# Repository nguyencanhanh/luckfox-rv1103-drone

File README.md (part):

# Drone AI trên RV1103 (Luckfox Pico Mini B)

Nguyên mẫu quadcopter dùng **một chip Rockchip RV1103**:
- **Cortex-A7 chạy Linux:** camera, NPU nhận dạng, Wi-Fi, GPS, bộ thu RC.
- **Lõi MCU RISC-V (HPMCU) chạy RT-Thread:** vòng điều khiển bay 1 kHz.

Mục tiêu dự án là trả lời bằng số liệu đo được: **kiến trúc một chip có bay được không**. Nếu không, phương án B là thêm một MCU điều khiển bay rời.

> **Trạng thái (2026-09-27):** chưa bay thật.
> - Linux và MCU đã chạy song song trên board, vòng 1 kHz đã đo.
> - Phần mềm bay chạy đầy đủ trong mô phỏng và lái được trong 3D.
> - Mạch bay LFX_FC_R1 đã thiết kế xong, chưa sản xuất.
> - Chưa có driver cảm biến thật, chưa xuất PWM ra ESC. Motor chưa bao giờ được cấp lệnh.

## Mục lục

- [Trạng thái theo mốc](#trạng-thái-theo-mốc)
- [Kiến trúc](#kiến-trúc)
- [Phần cứng: mạch bay LFX_FC_R2](#phần-cứng-mạch-bay-lfx_fc_r2)
- [Mô phỏng](#mô-phỏng)
- [Bắt đầu nhanh](#bắt-đầu-nhanh)
- [Cấu trúc repo](#cấu-trúc-repo)
- [An toàn](#an-toàn)
- [Tài liệu](#tài-liệu)
- [Nguồn tham khảo](#nguồn-tham-khảo)
- [License](#license)

## Trạng thái theo mốc

| Mốc | Nội dung | Kết quả | Bằng chứng |
|---|---|---|---|
| 01 | Điều tra phần cứng RV1103, HPMCU trong SDK | xong | [RV1103_MCU.md](docs/RV1103_MCU.md), [PERIPHERALS.md](docs/PERIPHERALS.md) |
| 02 | Build firmware Luckfox stock trên macOS | **PASS** | `logs/sdk_build.log`, [MILESTONE1.md](docs/MILESTONE1.md) |
| 03 | Build RT-Thread cho HPMCU | **PASS** | [MCU_BUILD.md](docs/MCU_BUILD.md) |
| 04 | MCU chạy song song Linux, vòng 1 kHz | **PASS trên board**: 2 × 1 000 000 vòng, 0 lỡ chu kỳ; jitter 18,2 µs lúc idle, 116,7 µs khi camera chạy | [REALTIME.md](docs/REALTIME.md) |
| — | Mạch bay LFX_FC_R1 (46 × 46 mm, 4 lớp) | thiết kế xong: ERC 0, DRC 0, 0 nối hở, khớp sơ đồ | [phần cứng](#phần-cứng-mạch-bay-lfx_fc_r1) |
| 05 | Phần mềm bay + mô phỏng SITL + 3D | **77/77 unit test, 10/10 kịch bản bay** (×2 profile cảm biến), kiểm thử bàn phím end-to-end 6/6 | [simulator/README.md](simulator/README.md) |
| 05b | Phần mềm bay chạy trên HPMCU với cảm biến giả (đo thời gian) | build xong (53 KB), **chưa chạy**: board chưa cắm | `tools/run_fc_mcu.sh` |
| 06–07 | Driver SPI + ICM-42688-P trên MCU | chưa làm: cần module IMU để kiểm | |
| 11 | Xuất PWM / DShot, đo bằng logic analyzer | chưa làm, **không gắn cánh** | |
| 12–13 | Điều khiển từ xa: IPC Linux ↔ MCU, `rc-bridge` (ELRS + mạng), trạm mặt đất có camera | **code xong, chuỗi đầy đủ chạy trên Mac 7/7**; build cho board xong, **chưa chạy trên board**; bộ thu ELRS cần chuyển console khỏi UART2 | [ground/README.md](ground/README.md) |
| M3 | Camera → NPU → nhận dạng, Wi-Fi, telemetry | chưa làm | |

Kế hoạch đầy đủ theo thứ tự an toàn ở mục [An toàn](#an-toàn).

## Kiến trúc

| Miền | Chạy gì | Sở hữu phần cứng |
|---|---|---|
| **HPMCU** RISC-V SCR1 297 MHz, `rv32imc` (không FPU), RT-Thread | vòng tốc độ quay 1 kHz, vòng góc 250 Hz, vòng độ cao 100 Hz, trộn motor, ARM / failsafe | SPI0 (IMU, barometer), PWM2 kênh 8–11 (4 ESC) |
| **Cortex-A7** 1,1 GHz, Linux (Buildroot của SDK) | đọc bộ thu RC (CRSF), camera + NPU, điều hướng, LTE + GPS (module Lierda), telemetry Wi-Fi, nạp firmware MCU và Lierda | UART2 (bộ thu RC), UART3 (Lierda: AT, GNSS, nạp firmware), chân 18/20 (RESET/BOOT Lierda), MIPI CSI, USB, SARADC, CRU |
| **DDR chung** 64 MB | MCU chạy ở `0x01800000` (256 KB, đã kiểm chứng); IPC đề xuất ở `0x01840000` | [MEMORY_MAP.md](docs/MEMORY_MAP.md) |

Luồng điều khiển:

```
IMU 1 kHz ─► hiệu chuẩn ─► lọc ─► Mahony (góc) + baro/accel (độ cao)
          ─► PID góc / độ cao ─► PID tốc độ quay ─► trộn quad-X ─► 4 motor (0..1)
tay điều khiển ELRS ─► bộ thu (CRSF 420 kbaud) ─► Linux ─► IPC ─► MCU (lệnh lái, ARM, chế độ)
```

Code bay (`mcu/`) là C99 thuần, chỉ dùng float, không cấp phát động. Cùng một mã nguồn build cho:
- máy Mac (mô phỏng);
- MCU (RT-Thread).

Chỗ đổi duy nhất là nguồn dữ liệu cảm biến:
- `SIM_SENSOR`: cảm biến giả trong mô phỏng;
- `REAL_SENSOR`: driver thật (bước 06–07).

Chi tiết và rủi ro: [ARCHITECTURE.md](docs/ARCHITECTURE.md), [architecture.html](docs/architecture.html).

**Rủi ro lớn nhất của kiến trúc một chip:**

| Rủi ro | Hệ quả |
|---|---|
| HPMCU không có FPU | code bay chạy bằng soft-float; phải đo thời gian thật |
| HAL MCU của RV1106 không có SPI và UART | phải tự viết driver |
| Tải camera làm jitter MCU tăng 6,4 lần | ảnh hưởng độ ổn định vòng điều khiển |
| Tín hiệu RC đi qua Linux | Linux treo là mất RC; MCU phải tự vào failsafe |

## Phần cứng: mạch bay LFX_FC_R2

**Một board 50 × 50 mm** gồm mạch bay cho Luckfox Pico Mini B và module **LTE Cat.1 bis + GNSS** (Lierda NT26-KCN E, khay nano-SIM, 2 cổng U.FL). Thiết kế bằng pipeline KiCad 10 viết bằng script, trong [`hardware/LFX_FC_R2/`](hardware/LFX_FC_R2): `design.py` → sơ đồ → PCB → file sản xuất.

| Mặt trên | Mặt dưới | 3D |
|---|---|---|
|  |  |  |

Module Lierda và đế cắm Luckfox chưa có mô hình 3D trong KiCad nên trên ảnh render chỉ thấy pad của chúng.

**Thông số:**
- **Kích thước:** 50 × 50 mm, 4 lớp: F.Cu tín hiệu / GND / VSYS (+ đảo 3,3 V cảm biến, đảo 3,8 V dưới module LTE, đảo GND dưới đường anten) / B.Cu.
- **Lỗ bắt vít:** 4 lỗ M3, khoảng cách lỗ **39 × 39 mm**, cách mép 5,5 mm.
- **Nguồn vào:** pin 2S–6S, hàn vào pad BAT+ / BAT− (mặt trên, phía trước bên phải).
- **Mạch nguồn:**
  - TVS SMAJ33A và ferrite chặn xung, lọc nhiễu.
  - Buck TPS54360 ra 5 V (theo thiết kế mẫu TI SLVSBB4G), ngưỡng UVLO 6,44 V. Đặt ở mặt dưới dải phải, cách IMU khoảng 15 mm, có lớp GND In1 ở giữa.
  - Diode lý tưởng LM66100 cấp VSYS cho Luckfox; LDO TLV75533 cấp 3,3 V riêng cho cảm biến.
  - Buck TLV62569 hạ +5 V xuống **3,8 V** cho module LTE. VBAT của module chỉ chịu 3,3–4,5 V, nên không lấy thẳng từ pin.
- **Cảm biến trên SPI0:** IMU ICM-42688-P và barometer BMP390, đặt dưới Luckfox; 4 đường SPI của IMU vẽ tay, không dùng via.
- **GPS ngoài (thêm 2026-10-04):** chân 14 (GPIO1_D2) thành **UART5_RX** cho cổng J18; chân chọn chip của barometer chuyển sang chân 15 (GPIO1_D3, MCU điều khiển như GPIO), bỏ chân ngắt dự phòng của IMU (IMU đọc kiểu polling). GNSS trong module Lierda vẫn giữ nguyên.
- **Motor:** 4 cặp pad S/G ở 4 góc cho **4 ESC rời** (PWM8–11, điện trở 47 Ω). Không còn cổng ESC 4-in-1.
- **LTE + GNSS: Lierda NT26-KCN E** ở mặt dưới, nửa trước. Khi đặt mua chọn bản **GPS + BDS**: bản NT26KCNE20GNB trong sổ tay phần cứng chỉ có BeiDou, chân ra giống hệt.
  - UART3 của Luckfox (chân 12/13) đi qua 2 con SN74LVC1T45 để chuyển 3,3 V ↔ 1,8 V. Chip này tự cách ly khi module tắt, vì UART của module không chịu điện áp ngược. Cùng một UART dùng cho lệnh AT, đọc GNSS và nạp firmware (921600 bd).
  - **Luckfox nạp firmware cho Lierda:** chân 18 kéo RESET_N qua MOSFET; chân 20 (GPIO4_C1, bank 1,8 V, cùng mức với module) nối USB_BOOT qua 1 kΩ. Giữ BOOT mức cao rồi reset ≥ 300 ms là module vào chế độ nạp. Có test pad USB (D+/D−/VBUS) để nạp cứu bằng máy tính.
  - Khay **nano-SIM** có nắp bản lề ở mặt trên, giữa phía trước; điện trở 22 Ω, tụ 33 pF, chống ESD TPD4E05U06.
  - 2 cổng U.FL ở 2 góc trước mặt dưới: GNSS bên trái, LTE bên phải. Đường 50 Ω rộng 0,35 mm trên B.Cu, có mạch π để chỉnh phối hợp trở kháng. GNSS cấp nguồn 3,3 V cho anten active; dùng anten thụ động thì bỏ R43.
  - Còi được điều khiển từ chân AGPIO5 (pad 97, ở mép module) của Lierda, vì Luckfox đã hết chân.
  - **Không bật chế độ ngủ của module** (`AT+QSCLK=1`): khi ngủ, VDD_EXT tắt nên bộ chuyển mức cách ly, Luckfox không đánh thức được qua UART.

**Đầu cắm và pad:**

| Cổng | Chân | Ghi chú |
|---|---|---|
| J2 / J3 · pad pin | BAT+ / BAT− | dây XT30 từ pin, cùng dây cấp cho 4 ESC |
| J4 · bộ thu RC ELRS | 1 5 V, 2 GND, 3 TX board → RX bộ thu, 4 RX board ← TX bộ thu | UART2, CRSF; R24 1 kΩ kéo lên để bộ thu không kẹt bootloader |
| J6 · còi | 1 +5 V, 2 còi − (MOSFET đóng ngắt) | gate do AGPIO5 của Lierda điều khiển |
| **J18 · module GPS ATGM336H** | 1 VCC +5 V, 2 GND, 3 TXD module → RX board, 4 RXD (không nối), 5 PPS (không nối) | header 2,54 mm 5 chân nằm ngang ở mép trái, **cùng thứ tự chân với module ATGM336H 5 chân**: thân nhựa trên board, chân cong chìa ra ngoài mép để cắm dây Dupont 5 sợi thẳng sang module (lọt dưới vỏ canopy). UART5 chỉ nhận (chân 14), NMEA 9600 mặc định; RXD và PPS bỏ trống vì Luckfox hết chân. Chống ESD TPD1E05U06 + 33 Ω. +5 V lấy từ buck TPS54360 (cùng nguồn với bộ thu RC J4, đường mặt dưới sát mép trái), nên GPS chỉ có điện khi cắm pin, không chạy khi chỉ cắm USB |
| J7–J14 · pad ESC | S / G ở 4 góc | M1 sau-phải, M2 trước-phải, M3 sau-trái, M4 trước-trái (Betaflight) |
| J15 · nano-SIM | | GCT SIM8060, nắp bản lề |
| J16 · U.FL LTE / J17 · U.FL GNSS | | mặt dưới, 2 góc trước |
| TP1–TP3, TP5, TP6 | +5 V, VSYS, +3V3S, RC_TX, RC_RX | TP5/TP6: xem console khi rút bộ thu |
| TP7–TP13 | +3V8, VDD_EXT 1,8 V, USB D+, USB D−, USB VBUS, DBG TX, DBG RX của Lierda | nạp cứu / xem log module |

**Kiểm tra:** ERC 0, DRC 0 vi phạm / 0 cảnh báo, 0 nối hở, 0 lỗi khớp sơ đồ (`--schematic-parity`).

**Bộ file sản xuất** (Gerber, khoan, BOM, vị trí linh kiện, STEP) do `make_fab.py` tạo ra `fab/`. Thư mục này không lưu trong git.

**Cần làm trước khi đặt hàng:**
- BOM chưa có mã linh kiện cụ thể (MPN).
- Nên chọn xi **ENIG**: IMU, barometer là chip chân LGA và module Lierda là LCC + LGA 109 chân, cần pad phẳng.

### Lắp drone: khung LFX_FRAME_R1, động cơ không chổi than, 4 ESC rời

| Khung (in 3D) | Lắp đủ: khung + board + vỏ + motor + ESC + pin | Nhìn từ trên |
|---|---|---|
|  |  |  |

**Khung [`hardware/LFX_FRAME_R1`](hardware/LFX_FRAME_R1)** dựng bằng FreeCAD (script tham số `frame_freecad.py`), in 3D, cho **motor 1503 + cánh 3,5"**:
- Tấm giữa dày 3 mm: board bắt thẳng bằng **4 cột M3 dài 8 mm** vào lỗ 39 × 39, không cần tấm chuyển. Có 2 khe dây buộc pin 15 mm, lỗ khoét giảm nhẹ, 2 lỗ phía sau để buộc ống anten. Mặt dưới tấm giữa phẳng để kê pin.
- 4 tay đòn kiểu X, dày 5 mm, rộng 13 mm. Đế motor Ø22 mm có **rãnh M2 hướng tâm** (bán kính 4,3–6,6 mm): lắp được motor 1503 (4 × M2 theo hình vuông 9 × 9 mm) và các motor có lỗ trên vòng Ø9 mm. Lỗ giữa Ø7 mm cho trục và phe gài.
- **Khoảng cách motor do script tự tìm:** đẩy dần motor ra xa cho tới khi cánh 3,5" (thêm 2 mm dự phòng) không chạm vỏ canopy. Kết quả: motor cách tâm 63 mm theo mỗi trục (đường chéo trục 178 mm), khung 148 × 148 mm.
- 4 ESC buộc dây rút lên tay đòn, nằm ngoài vỏ; pin buộc dưới tấm giữa.
- In: PETG (hoặc PLA-CF), 5 lớp viền, infill 40 %. Khối lượng đặc khoảng 34 g.
- Đổi motor hoặc cánh: sửa `PROP_D`, `MOTOR_D`, `MOTOR_SLOT` ở đầu `frame_freecad.py` rồi chạy lại trong FreeCAD; khoảng cách motor tự tính lại.

**Linh kiện mua thêm:**

| Linh kiện | Gợi ý | Ghi chú |
|---|---|---|
| Motor ×4 | 1503, bản KV dành cho cánh 3,5" và đúng số cell pin (người bán thường ghi "3.5 inch 3S" hoặc "4S") | khoảng 8–9 g/con; 4 × M2 lỗ 9 × 9 mm |
| ESC ×4 | ESC rời 20–30 A, BLHeli_S / BLHeli_32 / AM32, chịu 2–4S | 1503 + cánh 3,5" kéo dòng cao hơn hẳn 1103, ESC 12 A không đủ |
| Cánh | 3,5" (3520 / 3525, 2–3 lá), lỗ trục hợp motor | |
| Pin | LiPo 3S hoặc 4S 450–650 mAh, đầu XT30 | |
| Cột M3 | 4 × 8 mm (khung → board) | |
| Anten | LTE dạng dán (FPC) + GNSS 25 × 25 mm (active 3,3 V hoặc thụ động), đầu U.FL | anten GNSS đặt trong hốc trên nóc vỏ |

**Đấu nối:**
```
Pin 3S/4S ─ XT30 ─┬─ nguồn 4 ESC (đỏ / đen)
                  └─ BAT+ / BAT− (J2 / J3) trên board
ESC n: tín hiệu → pad S, mass tín hiệu → pad G ở góc của motor n
   M1 sau-phải J7/J11 · M2 trước-phải J8/J12 · M3 sau-trái J9/J13 · M4 trước-trái J10/J14
Motor: 3 dây vào ESC; quay ngược chiều thì đổi 2 dây bất kỳ
```
- Board chạy 2S–6S (buck 5 V khởi động từ 6,44 V), nên 3S và 4S đều dư.
- ESC rời không có chân báo dòng, nên chỉ đo được áp pin (ADC_VBAT), không đo được dòng.

**Trọng lượng ước tính** (chưa cân thực tế):
- Board R2 khoảng 16 g, Luckfox + camera khoảng 8 g, 4 ESC khoảng 24 g, 4 motor 1503 khoảng 36 g, khung khoảng 34 g, vỏ khoảng 13 g, cánh khoảng 6 g, anten + ốc + dây khoảng 8 g, pin 4S 450 mAh khoảng 55 g (3S khoảng 40 g).
- Tổng **khoảng 200 g với 4S** (khoảng 185 g với 3S).
- Theo [bảng tra của Oscar Liang](https://oscarliang.com/table-prop-motor-lipo-weight/), cánh 3–3,5" với motor cỡ 1404–1505 trên 3S–4S hợp drone nặng khoảng 150–300 g, nên cấu hình này nằm giữa dải, dư lực. Mình chưa có số đo lực đẩy cụ thể của 1503; hãy xem bảng lực đẩy của đúng mẫu motor khi mua.

### Vỏ in 3D: LFX_CANOPY_R1

| Vỏ | Nhìn xuyên (kiểm tra lắp) | Phía sau |
|---|---|---|
|  |  |  |

Vỏ che board, dựng bằng **FreeCAD 1.1** (script tham số [`canopy_freecad.py`](hardware/LFX_CANOPY_R1/canopy_freecad.py), chạy trong FreeCAD hoặc qua addon [freecad-mcp](https://github.com/neka-nat/freecad-mcp)). Script dựng cả cụm lắp ráp từ file STEP của board (KiCad) cộng khối đại diện cho Luckfox, camera, Lierda, cột đỡ, rồi **kiểm tra va chạm**: không chạm.

- File in: [`canopy.stl`](hardware/LFX_CANOPY_R1/canopy.stl) (và `canopy.step`), 58 × 60 × 29 mm, khoảng 13 g PETG.
- Thành 1,2 mm (3 lớp viền với đầu phun 0,4 mm), bo tròn mọi cạnh, lỗ ống kính vát mép.
- Camera SC3336 áp vào mặt trong thành trước, có gờ định vị 4 phía; cố định bằng băng dính 2 mặt hoặc keo nến.
- Lỗ USB-C phía sau, nên **vẫn cắm cáp nạp code cho Luckfox khi đã đậy vỏ**.
- Hai bên hông để trống phía dưới cho dây RC, còi, ESC, dây pin và cáp U.FL; khe thông gió ngay trên Luckfox.
- Trên nóc có hốc lõm 0,8 mm đặt anten GNSS loại 25 × 25 mm (nằm trên cùng, nhìn thẳng lên trời) và lỗ luồn cáp; mặt nóc vẫn phẳng để in úp.
- 4 trụ rỗng tì xuống board tại 4 lỗ 39 × 39; vít **M3 × 25** xuyên trụ, qua board, vào cột đỡ.
- In: úp nóc xuống bàn in, PETG, không cần support.
- Sửa kích thước: đổi tham số đầu file `canopy_freecad.py` rồi chạy lại trong FreeCAD. File STEP của board xuất bằng `kicad-cli pcb export step` vào `hardware/LFX_CANOPY_R1/step/`.

### Phiên bản cũ

Vẫn giữ trong repo, DRC sạch, nhưng không còn là thiết kế chính:
- [`LFX_FC_R1`](hardware/LFX_FC_R1): mạch bay 46 × 46 mm, cổng ESC 4-in-1 (J1), cổng J5 nối sang board LTE ([ảnh](docs/img/pcb/3d_iso.jpg)).
- [`LFX_LTE_R1`](hardware/LFX_LTE_R1): board LTE 46 × 46 mm xếp tầng trên R1 ([ảnh](docs/img/pcb/lte_3d_iso.jpg)).
- [`LFX_MOUNT_R1`](hardware/LFX_MOUNT_R1): tấm chuyển lỗ 39 × 39 → khung 20 × 20 / 25,5 × 25,5 mm, dùng khi lắp board lên khung mua sẵn thay cho LFX_FRAME_R1 ([ảnh](docs/img/pcb/mount_3d_iso.jpg)).

## Mô phỏng

Toàn bộ phần mềm bay chạy trên máy Mac, lái được bằng bàn phím hoặc tay điều khiển USB. Tín hiệu điều khiển đi qua đúng đường mà bộ thu thật sẽ đi: khung CRSF → bộ đọc CRSF → `fc_tick()`. Chi tiết: [simulator/README.md](simulator/README.md).

| | |
|---|---|
|  **ALT HOLD**, camera đuổi theo |  Vòng trong gió 6 m/s |
|  Người lái đứng dưới đất |  Camera FPV |
|  **Mất sóng RC** → tự hạ cánh |  **Từ chối ARM** khi ga chưa về 0 |

Dữ liệu từ chính các kịch bản kiểm thử (`tools/plot_sim.py`):

**Kết quả kiểm thử** (`make -C simulator test`):

| Kịch bản | Kết quả |
|---|---|
| giữ độ cao 10 s | sai số tối đa 0,25 m, nghiêng 0,2°, ước lượng góc sai 0,09° rms |
| bước nghiêng 15° | đạt 90 % trong 0,27 s, vọt lố 12 % |
| mất sóng RC ở 4 m | giữ thăng bằng sau 0,26 s, tự hạ sau 1,26 s, chạm đất và tự tắt motor, không rơi |
| IMU hỏng giữa trời | tắt motor sau 20 ms |
| gió 4,5 m/s + giật 2 m/s | độ cao sai < 0,3 m, nghiêng < 4° |
| lật 360° ở ACRO | đạt 418 °/s (yêu cầu 400), tự cân bằng lại, ước lượng góc vẫn đúng |
| bật ALT HOLD khi đang lên 9 m/s | phanh rồi khóa độ cao, sau 3 s lệch < 0,2 m |

**Giới hạn đã biết:**
- **Khung drone là giả định** (0,6 kg, 225 mm, 6 N/motor). Các hệ số PID chỉ là điểm xuất phát.
- **Chưa có GPS nên không giữ được vị trí.** Khi drone tăng tốc hoặc vào cua, góc ước lượng lệch 2–5°, vì accelerometer không phân biệt được nghiêng với gia tốc.
- **Thời gian chạy đo trên Mac không đại diện cho MCU.** Phải đo trên board.

## Điều khiển từ xa và camera

Trạm mặt đất trên Mac: video camera, đường chân trời nhân tạo, telemetry, lái bằng bàn phím hoặc tay điều khiển USB.
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
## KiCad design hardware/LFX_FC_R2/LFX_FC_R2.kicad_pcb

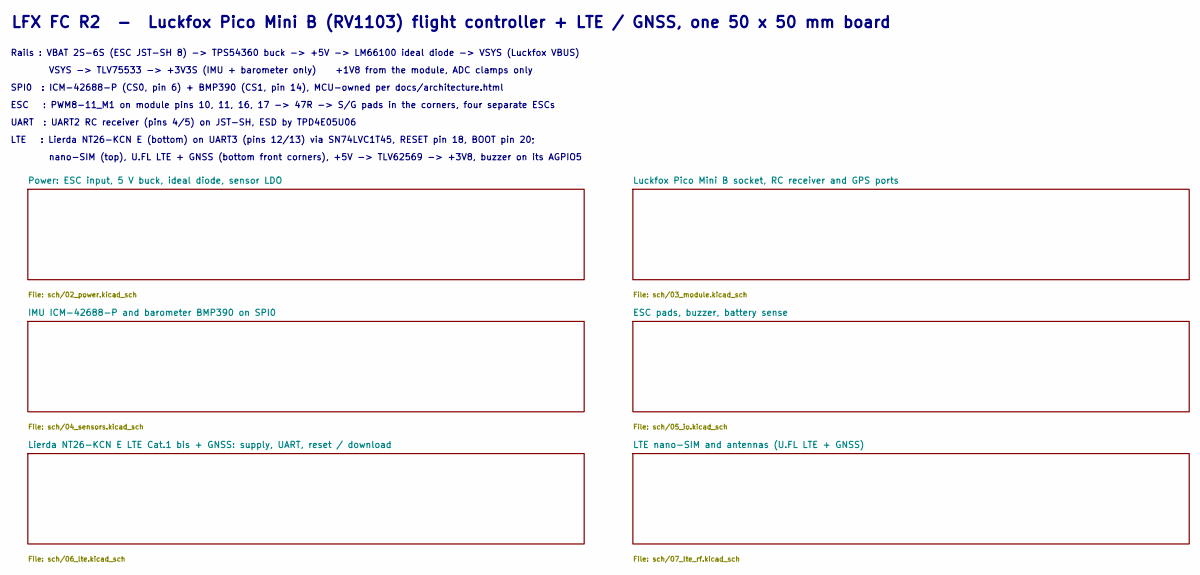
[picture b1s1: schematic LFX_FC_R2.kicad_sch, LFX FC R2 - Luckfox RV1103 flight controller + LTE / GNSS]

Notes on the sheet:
LFX FC R2 - Luckfox Pico Mini B (RV1103) flight controller + LTE / GNSS, one 50 x 50 mm board
Rails : VBAT 2S-6S (ESC JST-SH 8) -> TPS54360 buck -> +5V -> LM66100 ideal diode -> VSYS (Luckfox VBUS)
VSYS -> TLV75533 -> +3V3S (IMU + barometer only) +1V8 from the module, ADC clamps only
SPI0 : ICM-42688-P (CS0, pin 6) + BMP390 (CS1, pin 14), MCU-owned per docs/architecture.html
ESC : PWM8-11_M1 on module pins 10, 11, 16, 17 -> 47R -> S/G pads in the corners, four separate ESCs
UART : UART2 RC receiver (pins 4/5) on JST-SH, ESD by TPD4E05U06
LTE : Lierda NT26-KCN E (bottom) on UART3 (pins 12/13) via SN74LVC1T45, RESET pin 18, BOOT pin 20;
nano-SIM (top), U.FL LTE + GNSS (bottom front corners), +5V -> TLV62569 -> +3V8, buzzer on its AGPIO5

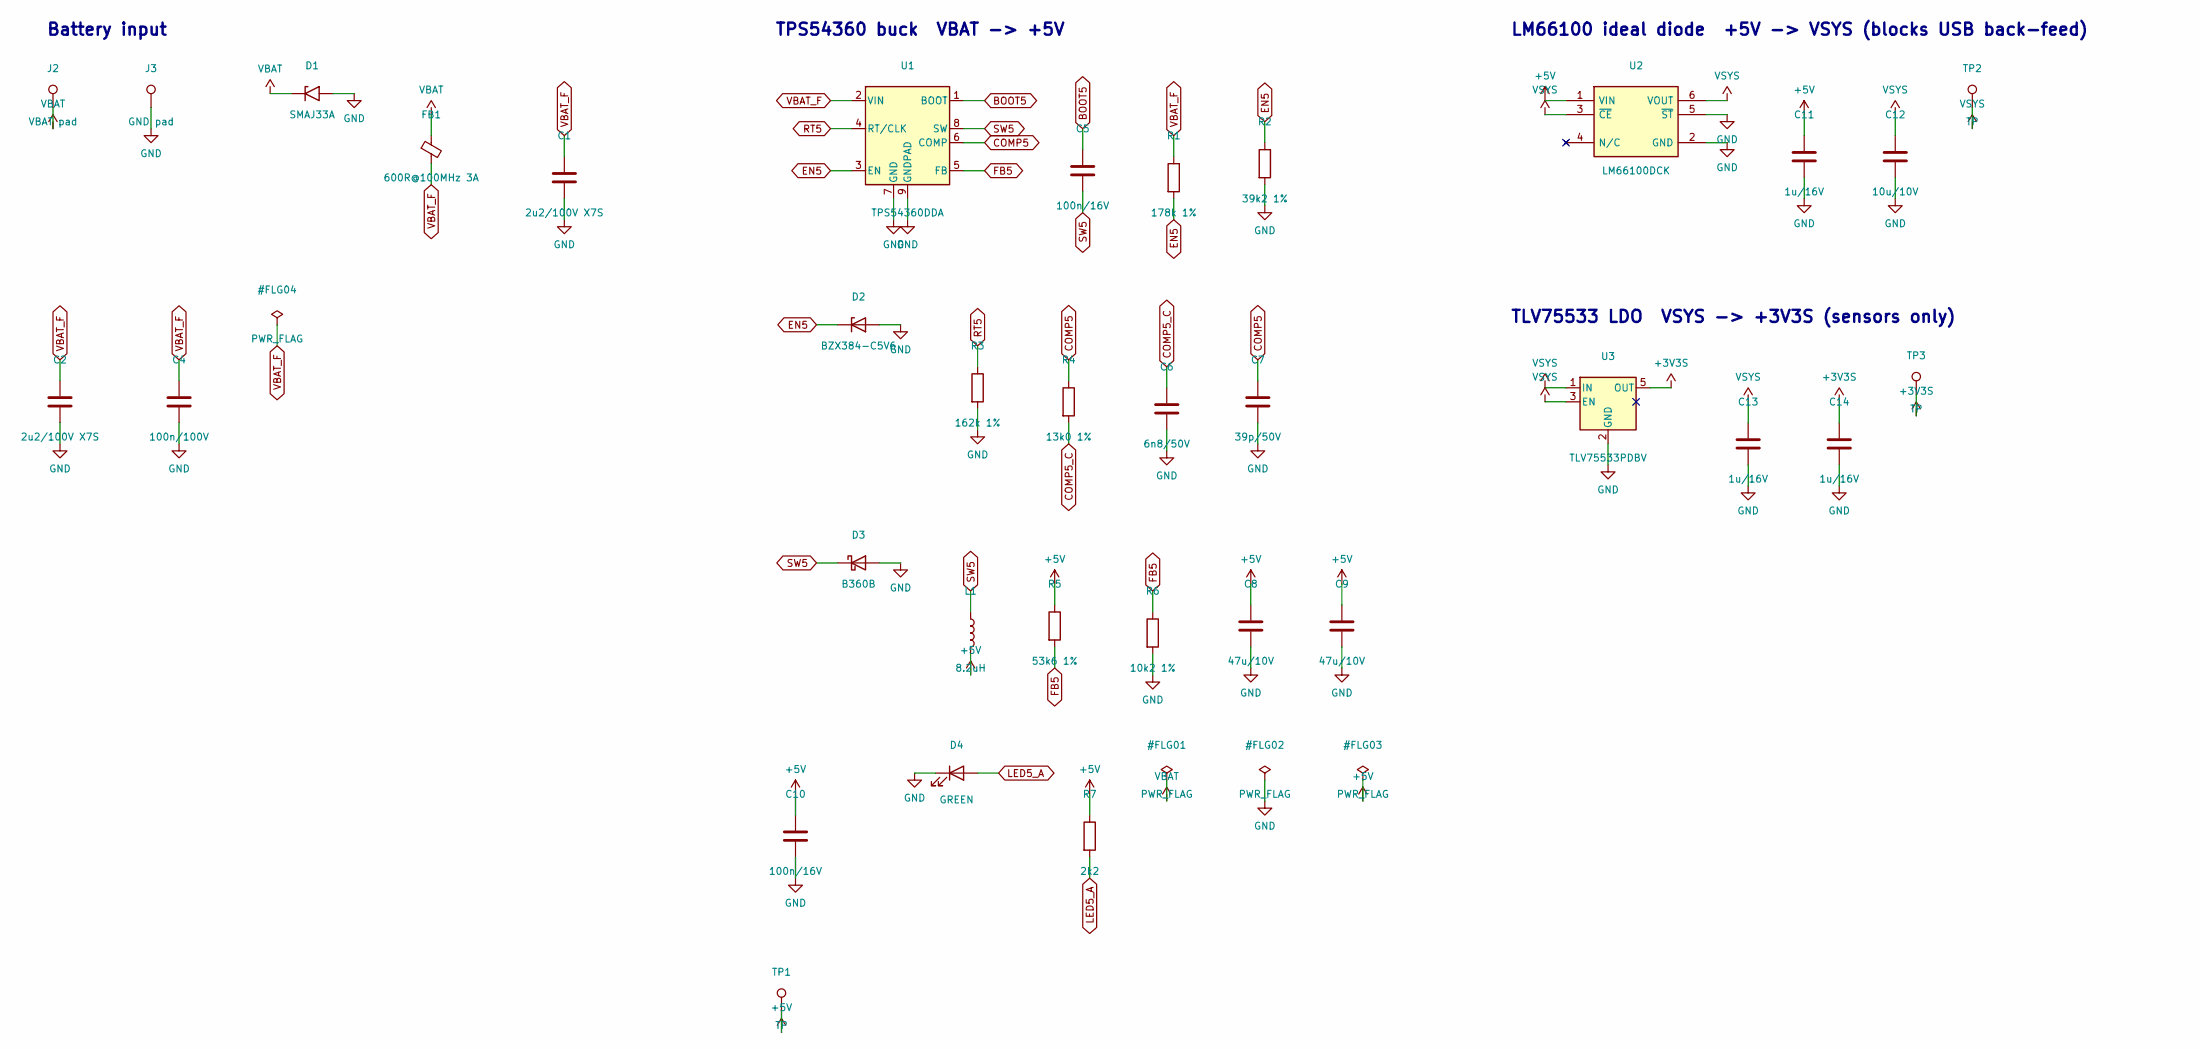
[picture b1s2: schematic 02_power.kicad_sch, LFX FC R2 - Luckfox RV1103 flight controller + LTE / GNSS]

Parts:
C1, C2: 2u2/100V X7S; C_1206_3216Metric
C4: 100n/100V; C_0603_1608Metric
C5, C10: 100n/16V; C_0603_1608Metric
C6: 6n8/50V; C_0402_1005Metric
C7: 39p/50V; C_0402_1005Metric
C8, C9: 47u/10V; C_1210_3225Metric
C11, C13, C14: 1u/16V; C_0603_1608Metric
C12: 10u/10V; C_0805_2012Metric
D1: SMAJ33A; D_SMA
D2: BZX384-C5V6; D_SOD-323
D3: B360B; D_SMB
D4: GREEN; LED_0603_1608Metric
FB1: 600R@100MHz 3A; L_1206_3216Metric
J2: VBAT pad; SolderPad_2.5x4mm
J3: GND pad; SolderPad_2.5x4mm
L1: 8.2uH; L_Coilcraft_XAL5050-XXX
R1: 178k 1%; R_0603_1608Metric
R2: 39k2 1%; R_0603_1608Metric
R3: 162k 1%; R_0603_1608Metric
R4: 13k0 1%; R_0402_1005Metric
R5: 53k6 1%; R_0402_1005Metric
R6: 10k2 1%; R_0402_1005Metric
R7: 2k2; R_0603_1608Metric
TP1, TP2, TP3: TP; TestPad_1.0mm
U1: TPS54360DDA; TI_SO-PowerPAD-8_ThermalVias
U2: LM66100DCK; SOT-363_SC-70-6
U3: TLV75533PDBV; SOT-23-5

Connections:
+3V3S: C14.1, TP3.1, U3.5 (OUT); also elsewhere on the board
+5V: C8.1, C9.1, C10.1, C11.1, L1.2, R5.1, R7.1, TP1.1, U2.1 (VIN); also elsewhere on the board
BOOT5: C5.1, U1.1 (BOOT)
COMP5: C7.1, R4.1, U1.6 (COMP)
COMP5_C: C6.1, R4.2
EN5: D2.1 (K), R1.2, R2.1, U1.3 (EN)
FB5: R5.2, R6.1, U1.5 (FB)
GND: C1.2, C2.2, C4.2, C6.2, C7.2, C8.2, C9.2, C10.2, C11.2, C12.2, C13.2, C14.2, D1.2 (A2), D2.2 (A), D3.2 (A), D4.1 (K), J3.1, R2.2, R3.2, R6.2, U1.7 (GND), U1.9 (GNDPAD), U2.2 (GND), U2.5 (~ST), U3.2 (GND); also elsewhere on the board
LED5_A: D4.2 (A), R7.2
RT5: R3.1, U1.4 (RT/CLK)
SW5: C5.2, D3.1 (K), L1.1, U1.8 (SW)
VBAT: D1.1 (A1), FB1.1, J2.1; also elsewhere on the board
VBAT_F: C1.1, C2.1, C4.1, FB1.2, R1.1, U1.2 (VIN)
VSYS: C12.1, C13.1, TP2.1, U2.3 (~CE), U2.6 (VOUT), U3.1 (IN), U3.3 (EN); also elsewhere on the board

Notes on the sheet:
Battery input
TPS54360 buck VBAT -> +5V
LM66100 ideal diode +5V -> VSYS (blocks USB back-feed)
TLV75533 LDO VSYS -> +3V3S (sensors only)

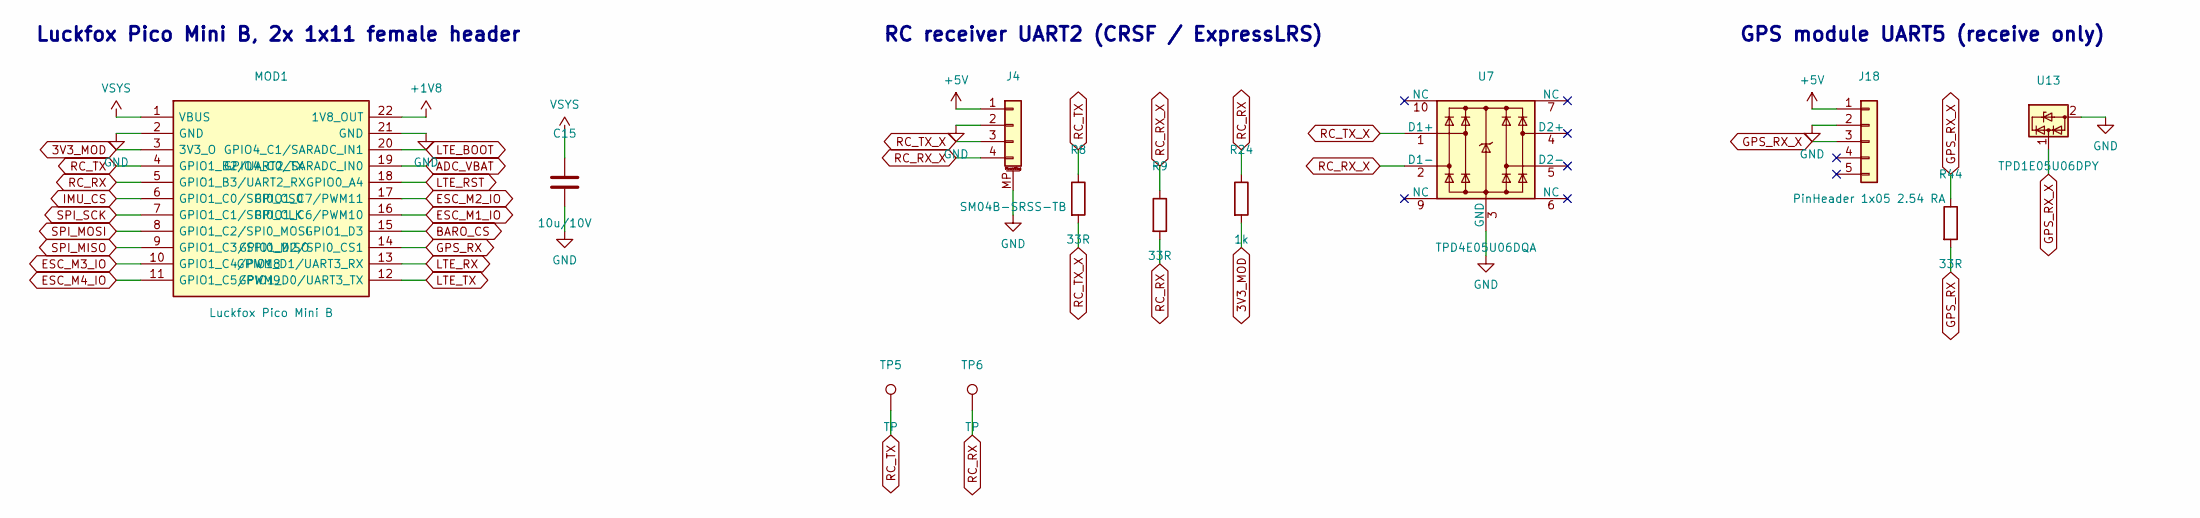
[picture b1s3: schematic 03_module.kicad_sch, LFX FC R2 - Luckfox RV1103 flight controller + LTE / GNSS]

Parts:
C15: 10u/10V; C_0805_2012Metric
J4: SM04B-SRSS-TB; JST_SH_SM04B-SRSS-TB_1x04-1MP_P1.00mm_Horizontal
J18: PinHeader 1x05 2.54 RA; PinHeader_1x05_P2.54mm_EdgeHorizontal
MOD1: Luckfox Pico Mini B; Luckfox_Pico_Mini_Socket
R8, R9, R44: 33R; R_0402_1005Metric
R24: 1k; R_0402_1005Metric
TP5, TP6: TP; TestPad_1.0mm
U7: TPD4E05U06DQA; USON-10_2.5x1.0mm_P0.5mm
U13: TPD1E05U06DPY; Texas_DPY0002A_0.6x1mm_P0.65mm

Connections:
3V3_MOD: MOD1.3 (3V3_O), R24.2; also elsewhere on the board
+1V8: MOD1.22 (1V8_OUT); also elsewhere on the board
+5V: J4.1, J18.1; also elsewhere on the board
ADC_VBAT: MOD1.19 (GPIO4_C0/SARADC_IN0); also elsewhere on the board
BARO_CS: MOD1.15 (GPIO1_D3); also elsewhere on the board
ESC_M1_IO: MOD1.16 (GPIO1_C6/PWM10); also elsewhere on the board
ESC_M2_IO: MOD1.17 (GPIO1_C7/PWM11); also elsewhere on the board
ESC_M3_IO: MOD1.10 (GPIO1_C4/PWM8); also elsewhere on the board
ESC_M4_IO: MOD1.11 (GPIO1_C5/PWM9); also elsewhere on the board
GND: C15.2, J4.2, J4.MP (MountPin), J18.2, MOD1.2 (GND), MOD1.21 (GND), U7.3 (GND), U7.8 (GND), U13.2 (GND); also elsewhere on the board
GPS_RX: MOD1.14 (GPIO1_D2/SPI0_CS1), R44.2
GPS_RX_X: J18.3, R44.1, U13.1 (I/O)
IMU_CS: MOD1.6 (GPIO1_C0/SPI0_CS0); also elsewhere on the board
LTE_BOOT: MOD1.20 (GPIO4_C1/SARADC_IN1); also elsewhere on the board
LTE_RST: MOD1.18 (GPIO0_A4); also elsewhere on the board
LTE_RX: MOD1.13 (GPIO1_D1/UART3_RX); also elsewhere on the board
LTE_TX: MOD1.12 (GPIO1_D0/UART3_TX); also elsewhere on the board
RC_RX: MOD1.5 (GPIO1_B3/UART2_RX), R9.2, R24.1, TP6.1
RC_RX_X: J4.4, R9.1, U7.2 (D1-)
RC_TX: MOD1.4 (GPIO1_B2/UART2_TX), R8.1, TP5.1
RC_TX_X: J4.3, R8.2, U7.1 (D1+)
SPI_MISO: MOD1.9 (GPIO1_C3/SPI0_MISO); also elsewhere on the board
SPI_MOSI: MOD1.8 (GPIO1_C2/SPI0_MOSI); also elsewhere on the board
SPI_SCK: MOD1.7 (GPIO1_C1/SPI0_CLK); also elsewhere on the board
VSYS: C15.1, MOD1.1 (VBUS); also elsewhere on the board

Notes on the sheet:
Luckfox Pico Mini B, 2x 1x11 female header
RC receiver UART2 (CRSF / ExpressLRS)
GPS module UART5 (receive only)

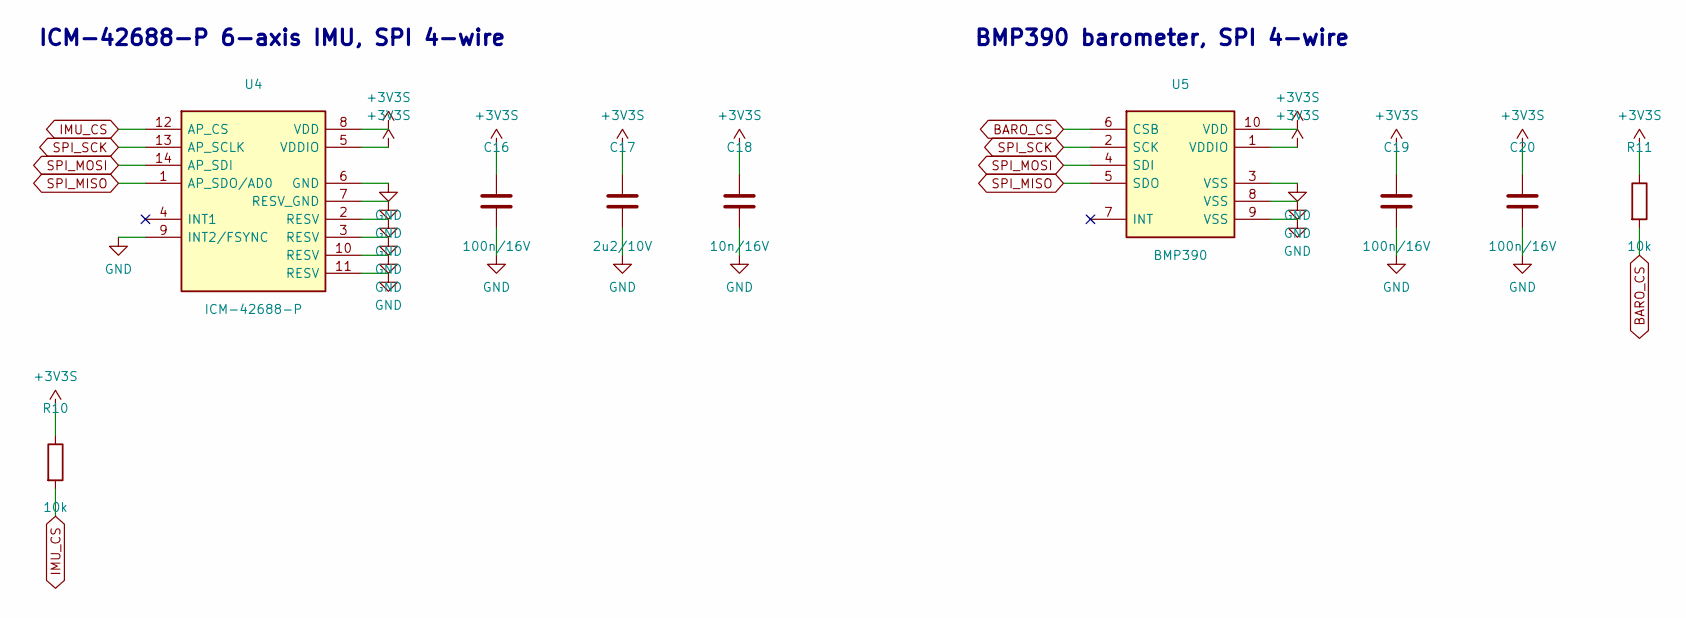
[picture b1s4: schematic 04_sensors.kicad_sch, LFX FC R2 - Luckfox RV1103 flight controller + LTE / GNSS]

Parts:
C16, C19, C20: 100n/16V; C_0402_1005Metric
C17: 2u2/10V; C_0402_1005Metric
C18: 10n/16V; C_0402_1005Metric
R10, R11: 10k; R_0402_1005Metric
U4: ICM-42688-P; LGA-14_3x2.5mm_P0.5mm_LayoutBorder3x4y
U5: BMP390; Bosch_BMP390_LGA-10_2x2mm_P0.5mm

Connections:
+3V3S: C16.1, C17.1, C18.1, C19.1, C20.1, R10.1, R11.1, U4.5 (VDDIO), U4.8 (VDD), U5.1 (VDDIO), U5.10 (VDD); also elsewhere on the board
BARO_CS: R11.2, U5.6 (CSB); also elsewhere on the board
GND: C16.2, C17.2, C18.2, C19.2, C20.2, U4.2 (RESV), U4.3 (RESV), U4.6 (GND), U4.7 (RESV_GND), U4.9 (INT2/FSYNC), U4.10 (RESV), U4.11 (RESV), U5.3 (VSS), U5.8 (VSS), U5.9 (VSS); also elsewhere on the board
IMU_CS: R10.2, U4.12 (AP_CS); also elsewhere on the board
SPI_MISO: U4.1 (AP_SDO/AD0), U5.5 (SDO); also elsewhere on the board
SPI_MOSI: U4.14 (AP_SDI), U5.4 (SDI); also elsewhere on the board
SPI_SCK: U4.13 (AP_SCLK), U5.2 (SCK); also elsewhere on the board

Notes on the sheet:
ICM-42688-P 6-axis IMU, SPI 4-wire
BMP390 barometer, SPI 4-wire

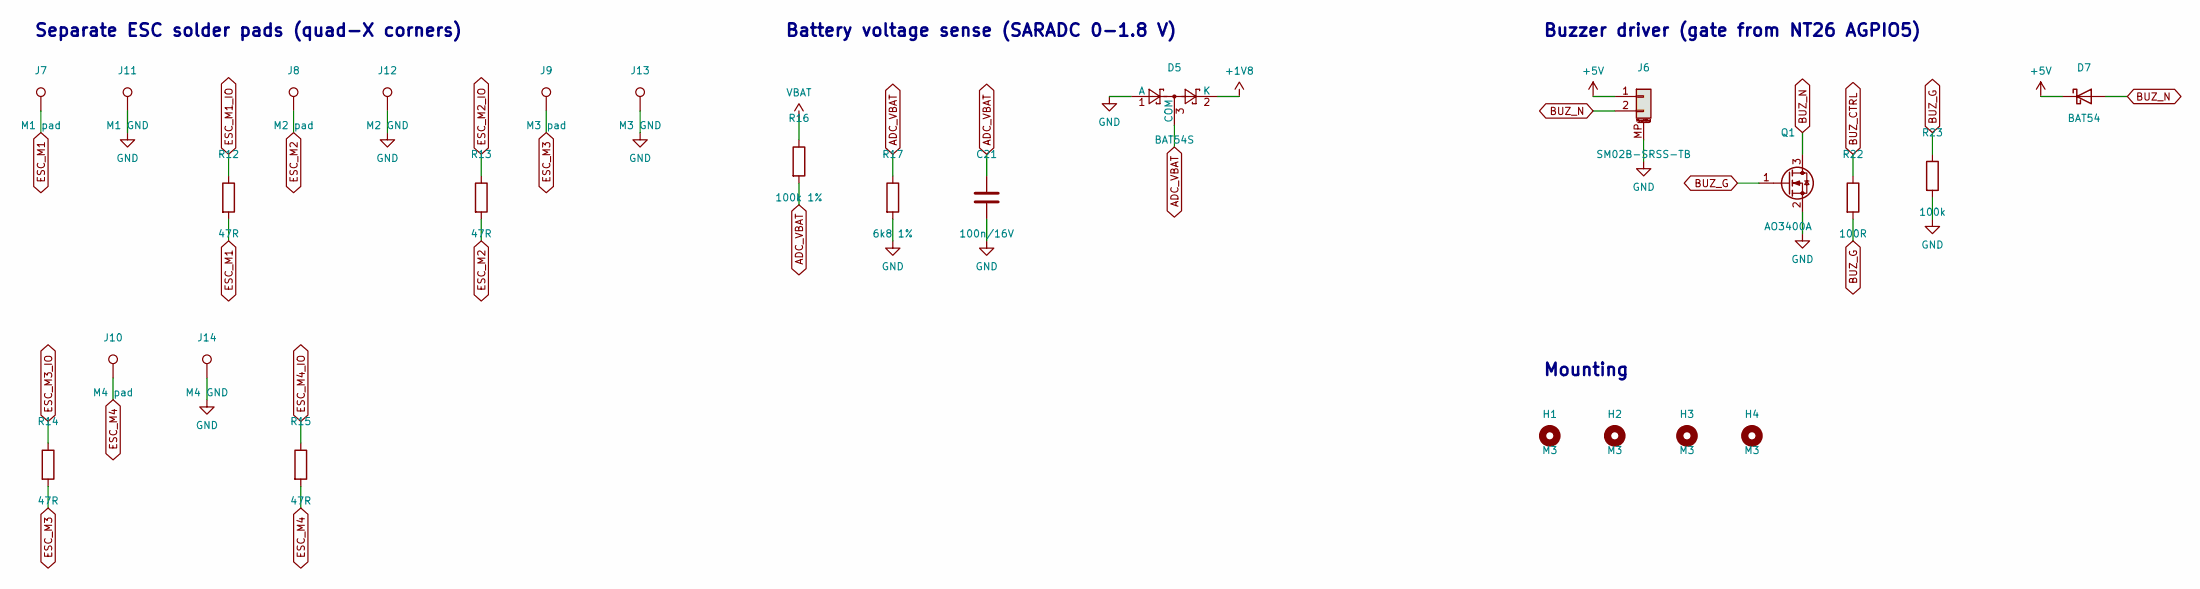
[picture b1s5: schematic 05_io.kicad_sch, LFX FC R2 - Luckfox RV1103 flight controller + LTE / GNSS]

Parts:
C21: 100n/16V; C_0402_1005Metric
D5: BAT54S; SOT-23
D7: BAT54; D_SOD-323
H1, H2, H3, H4: M3; MountingHole_3.2mm_M3
J6: SM02B-SRSS-TB; JST_SH_SM02B-SRSS-TB_1x02-1MP_P1.00mm_Horizontal
J7: M1 pad; SolderPad_1.5x2.5mm
J8: M2 pad; SolderPad_1.5x2.5mm
J9: M3 pad; SolderPad_1.5x2.5mm
J10: M4 pad; SolderPad_1.5x2.5mm
J11: M1 GND; SolderPad_1.5x2.5mm
J12: M2 GND; SolderPad_1.5x2.5mm
J13: M3 GND; SolderPad_1.5x2.5mm
J14: M4 GND; SolderPad_1.5x2.5mm
Q1: AO3400A; SOT-23
R12, R13, R14, R15: 47R; R_0402_1005Metric
R16: 100k 1%; R_0603_1608Metric
R17: 6k8 1%; R_0603_1608Metric
R22: 100R; R_0402_1005Metric
R23: 100k; R_0402_1005Metric

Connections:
+1V8: D5.2 (K); also elsewhere on the board
+5V: D7.1 (K), J6.1; also elsewhere on the board
ADC_VBAT: C21.1, D5.3 (COM), R16.2, R17.1; also elsewhere on the board
BUZ_CTRL: R22.1; also elsewhere on the board
BUZ_G: Q1.1 (G), R22.2, R23.1
BUZ_N: D7.2 (A), J6.2, Q1.3 (D)
ESC_M1: J7.1, R12.2
ESC_M1_IO: R12.1; also elsewhere on the board
ESC_M2: J8.1, R13.2
ESC_M2_IO: R13.1; also elsewhere on the board
ESC_M3: J9.1, R14.2
ESC_M3_IO: R14.1; also elsewhere on the board
ESC_M4: J10.1, R15.2
ESC_M4_IO: R15.1; also elsewhere on the board
GND: C21.2, D5.1 (A), J6.MP (MountPin), J11.1, J12.1, J13.1, J14.1, Q1.2 (S), R17.2, R23.2; also elsewhere on the board
VBAT: R16.1; also elsewhere on the board

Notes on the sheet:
Separate ESC solder pads (quad-X corners)
Battery voltage sense (SARADC 0-1.8 V)
Buzzer driver (gate from NT26 AGPIO5)
Mounting

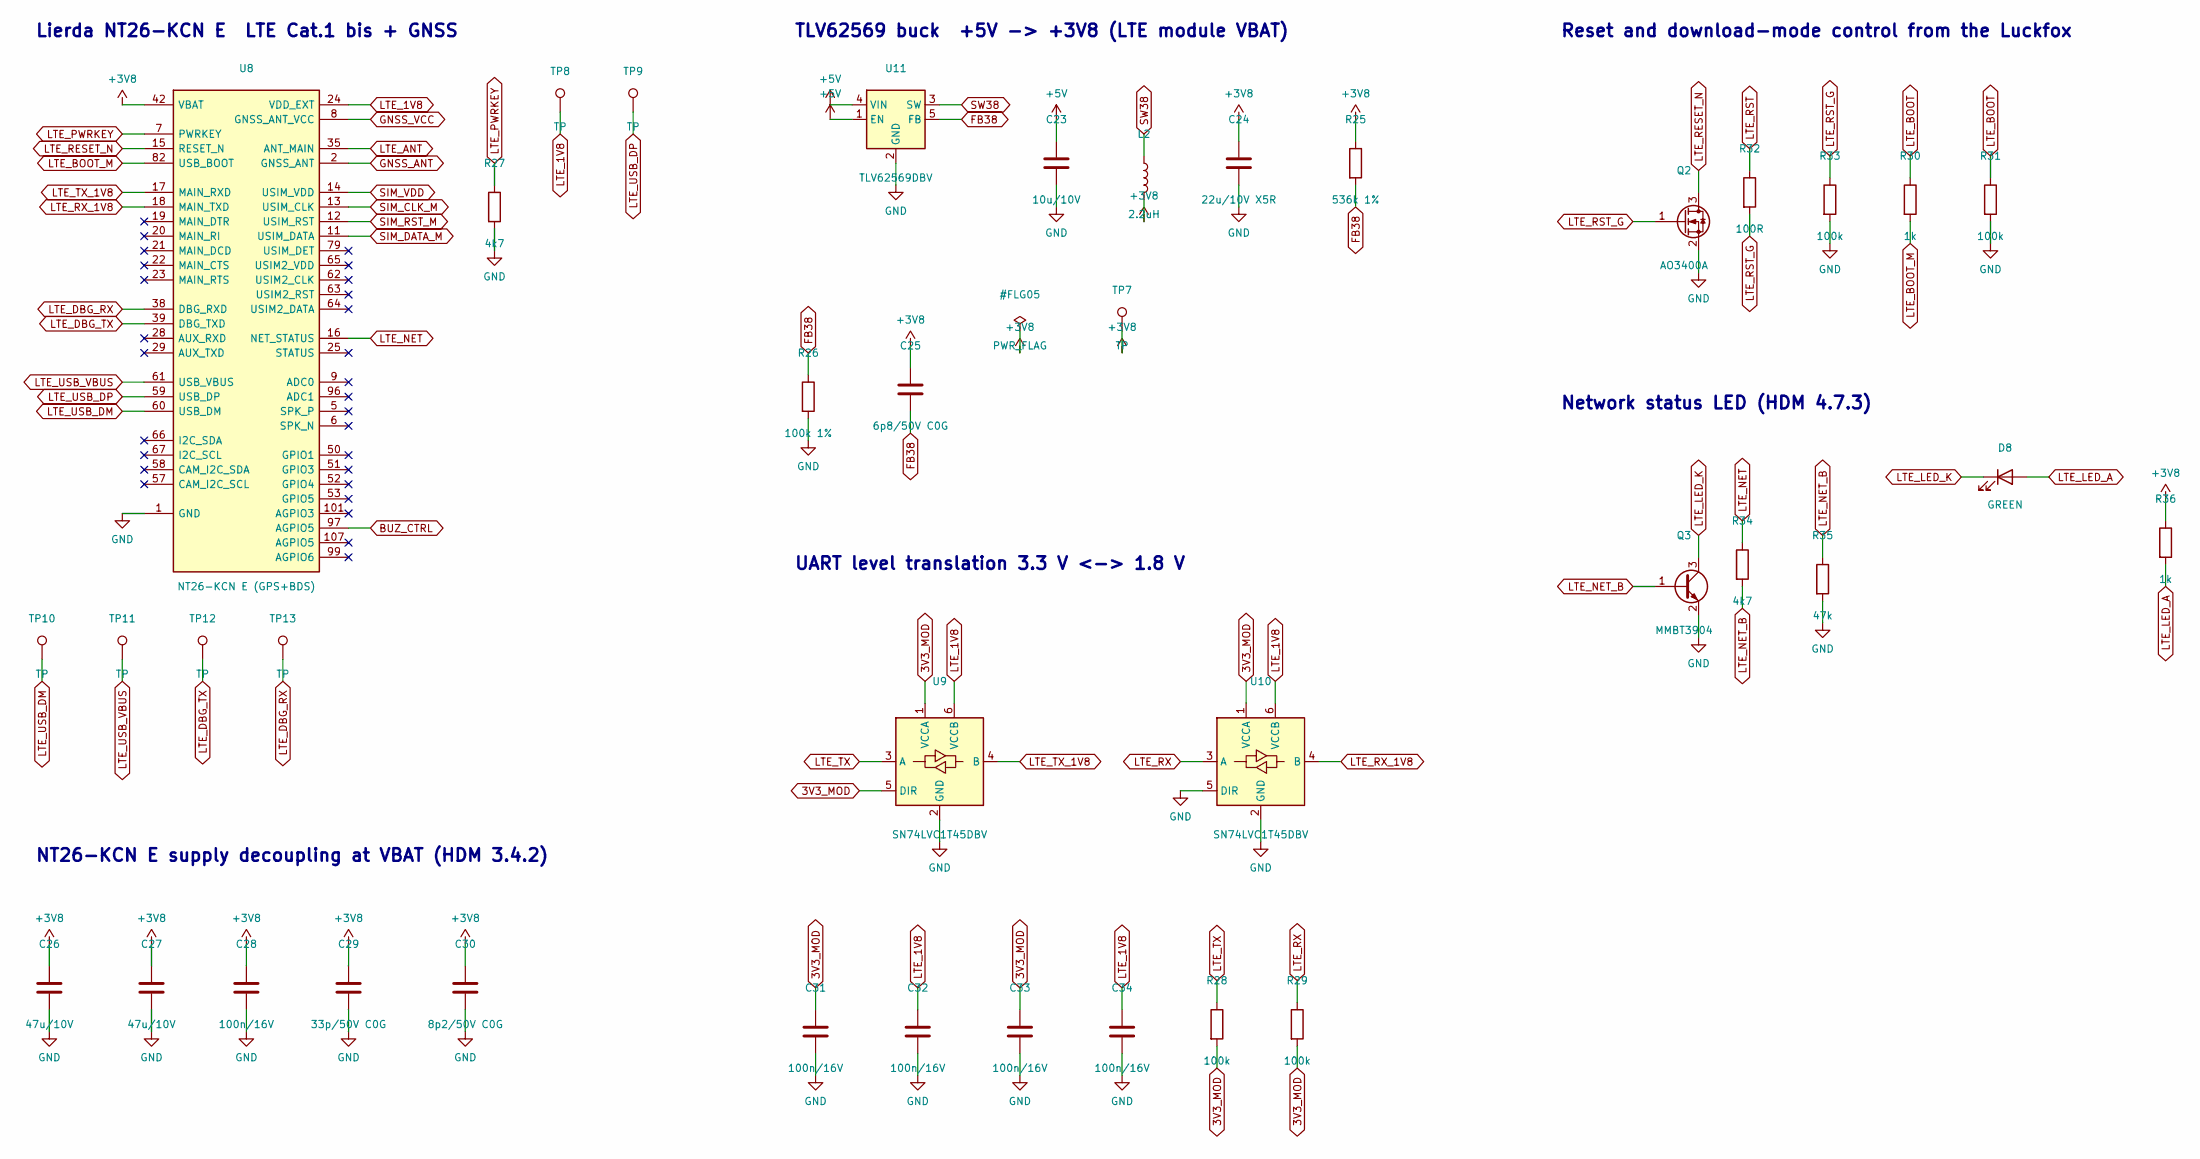
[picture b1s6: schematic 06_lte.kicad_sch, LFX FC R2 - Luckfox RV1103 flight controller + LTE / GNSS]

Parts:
C23: 10u/10V; C_0805_2012Metric
C24: 22u/10V X5R; C_1206_3216Metric
C25: 6p8/50V C0G; C_0402_1005Metric
C26, C27: 47u/10V; C_1210_3225Metric
C28, C31, C32, C33, C34: 100n/16V; C_0402_1005Metric
C29: 33p/50V C0G; C_0402_1005Metric
C30: 8p2/50V C0G; C_0402_1005Metric
D8: GREEN; LED_0603_1608Metric
L2: 2.2uH; L_Coilcraft_XAL4020-XXX
Q2: AO3400A; SOT-23
Q3: MMBT3904; SOT-23
R25: 536k 1%; R_0402_1005Metric
R26: 100k 1%; R_0402_1005Metric
R27, R34: 4k7; R_0402_1005Metric
R28, R29, R31, R33: 100k; R_0402_1005Metric
R30, R36: 1k; R_0402_1005Metric
R32: 100R; R_0402_1005Metric
R35: 47k; R_0402_1005Metric
TP7, TP8, TP9, TP10, TP11, TP12, TP13: TP; TestPad_1.0mm
U8: NT26-KCN E (GPS+BDS); Lierda_NT26-KCN_LCC-LGA-109_15.8x17.7mm
U9, U10: SN74LVC1T45DBV; SOT-23-6
U11: TLV62569DBV; SOT-23-5

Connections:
3V3_MOD: C31.1, C33.1, R28.2, R29.2, U9.1 (VCCA), U9.5 (DIR), U10.1 (VCCA); also elsewhere on the board
+3V8: C24.1, C25.1, C26.1, C27.1, C28.1, C29.1, C30.1, L2.2, R25.1, R36.1, TP7.1, U8.42 (VBAT), U8.43 (VBAT)
+5V: C23.1, U11.1 (EN), U11.4 (VIN); also elsewhere on the board
BUZ_CTRL: U8.97 (AGPIO5); also elsewhere on the board
FB38: C25.2, R25.2, R26.1, U11.5 (FB)
GND: C23.2, C24.2, C26.2, C27.2, C28.2, C29.2, C30.2, C31.2, C32.2, C33.2, C34.2, Q2.2 (S), Q3.2 (E), R26.2, R27.2, R31.2, R33.2, R35.2, U8.1 (GND), U8.10 (GND), U8.27 (GND), U8.34 (GND), U8.36 (GND), U8.37 (GND), U8.40 (GND), U8.41 (GND), U8.45 (GND), U8.46 (GND), U8.47 (GND), U8.48 (GND), U8.70 (GND), U8.71 (GND), U8.72 (GND), U8.73 (GND), U8.88 (GND), U8.89 (GND), U8.90 (GND), U8.91 (GND), U8.92 (GND), U8.93 (GND), U8.94 (GND), U8.95 (GND), U9.2 (GND), U10.2 (GND), U10.5 (DIR), U11.2 (GND); also elsewhere on the board
GNSS_ANT: U8.2 (GNSS_ANT); also elsewhere on the board
GNSS_VCC: U8.8 (GNSS_ANT_VCC); also elsewhere on the board
LTE_1V8: C32.1, C34.1, TP8.1, U8.24 (VDD_EXT), U9.6 (VCCB), U10.6 (VCCB)
LTE_ANT: U8.35 (ANT_MAIN); also elsewhere on the board
LTE_BOOT: R30.1, R31.1; also elsewhere on the board
LTE_BOOT_M: R30.2, U8.82 (USB_BOOT)
LTE_DBG_RX: TP13.1, U8.38 (DBG_RXD)
LTE_DBG_TX: TP12.1, U8.39 (DBG_TXD)
LTE_LED_A: D8.2 (A), R36.2
LTE_LED_K: D8.1 (K), Q3.3 (C)
LTE_NET: R34.1, U8.16 (NET_STATUS)
LTE_NET_B: Q3.1 (B), R34.2, R35.1
LTE_PWRKEY: R27.1, U8.7 (PWRKEY)
LTE_RESET_N: Q2.3 (D), U8.15 (RESET_N)
LTE_RST: R32.1; also elsewhere on the board
LTE_RST_G: Q2.1 (G), R32.2, R33.1
LTE_RX: R29.1, U10.3 (A); also elsewhere on the board
LTE_RX_1V8: U8.18 (MAIN_TXD), U10.4 (B)
LTE_TX: R28.1, U9.3 (A); also elsewhere on the board
LTE_TX_1V8: U8.17 (MAIN_RXD), U9.4 (B)
LTE_USB_DM: TP10.1, U8.60 (USB_DM)
LTE_USB_DP: TP9.1, U8.59 (USB_DP)
LTE_USB_VBUS: TP11.1, U8.61 (USB_VBUS)
SIM_CLK_M: U8.13 (USIM_CLK); also elsewhere on the board
SIM_DATA_M: U8.11 (USIM_DATA); also elsewhere on the board
SIM_RST_M: U8.12 (USIM_RST); also elsewhere on the board
SIM_VDD: U8.14 (USIM_VDD); also elsewhere on the board
SW38: L2.1, U11.3 (SW)

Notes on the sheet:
Lierda NT26-KCN E LTE Cat.1 bis + GNSS
NT26-KCN E supply decoupling at VBAT (HDM 3.4.2)
TLV62569 buck +5V -> +3V8 (LTE module VBAT)
UART level translation 3.3 V <-> 1.8 V
Reset and download-mode control from the Luckfox
Network status LED (HDM 4.7.3)

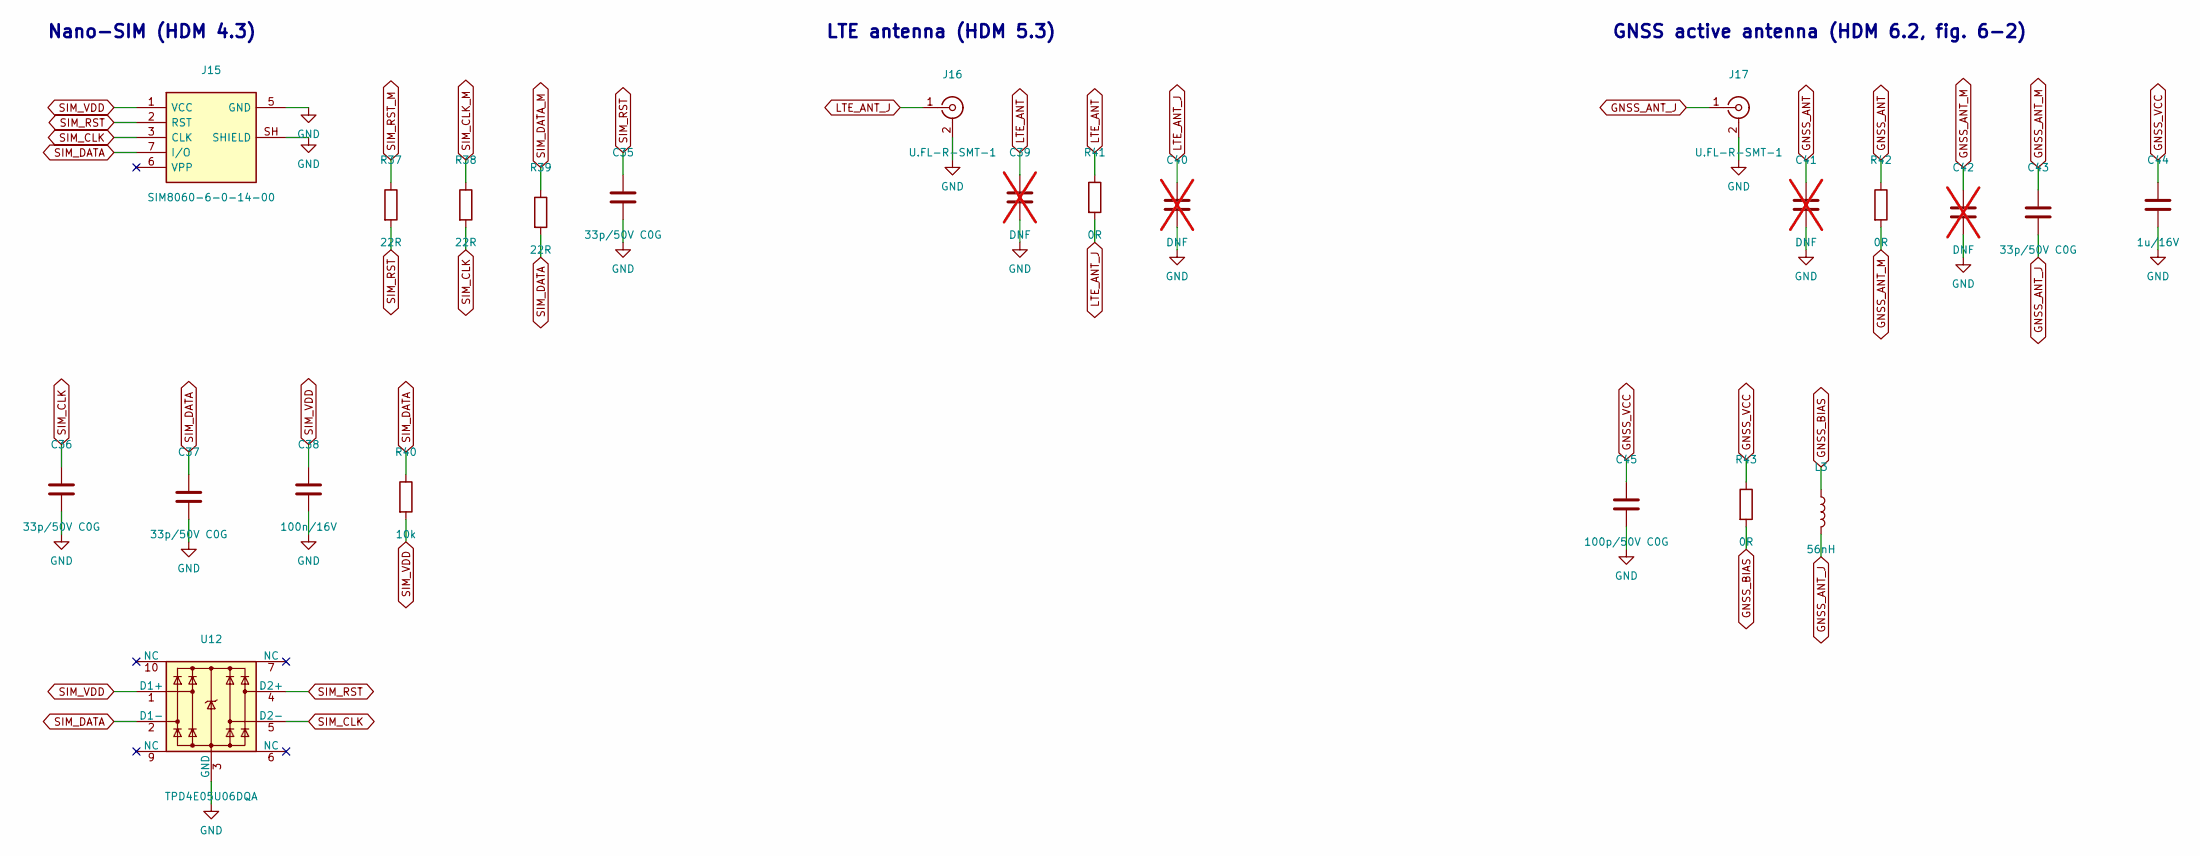
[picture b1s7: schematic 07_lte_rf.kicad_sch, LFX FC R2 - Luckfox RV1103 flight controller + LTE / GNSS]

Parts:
C35, C36, C37, C43: 33p/50V C0G; C_0402_1005Metric
C38: 100n/16V; C_0402_1005Metric
C39, C40, C41, C42: DNF; C_0402_1005Metric; not fitted
C44: 1u/16V; C_0402_1005Metric
C45: 100p/50V C0G; C_0402_1005Metric
J15: SIM8060-6-0-14-00; nanoSIM_GCT_SIM8060-6-0-14-00
J16, J17: U.FL-R-SMT-1; U.FL_Hirose_U.FL-R-SMT-1_Vertical
L3: 56nH; L_0402_1005Metric
R37, R38, R39: 22R; R_0402_1005Metric
R40: 10k; R_0402_1005Metric
R41, R42, R43: 0R; R_0402_1005Metric
U12: TPD4E05U06DQA; USON-10_2.5x1.0mm_P0.5mm

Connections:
GND: C35.2, C36.2, C37.2, C38.2, C39.2, C40.2, C41.2, C42.2, C44.2, C45.2, J15.5 (GND), J15.SH (SHIELD), J16.2 (Ext), J17.2 (Ext), U12.3 (GND), U12.8 (GND); also elsewhere on the board
GNSS_ANT: C41.1, R42.1; also elsewhere on the board
GNSS_ANT_J: C43.2, J17.1 (In), L3.2
GNSS_ANT_M: C42.1, C43.1, R42.2
GNSS_BIAS: L3.1, R43.2
GNSS_VCC: C44.1, C45.1, R43.1; also elsewhere on the board
LTE_ANT: C39.1, R41.1; also elsewhere on the board
LTE_ANT_J: C40.1, J16.1 (In), R41.2
SIM_CLK: C36.1, J15.3 (CLK), R38.2, U12.5 (D2-)
SIM_CLK_M: R38.1; also elsewhere on the board
SIM_DATA: C37.1, J15.7 (I/O), R39.2, R40.1, U12.2 (D1-)
SIM_DATA_M: R39.1; also elsewhere on the board
SIM_RST: C35.1, J15.2 (RST), R37.2, U12.4 (D2+)
SIM_RST_M: R37.1; also elsewhere on the board
SIM_VDD: C38.1, J15.1 (VCC), R40.2, U12.1 (D1+); also elsewhere on the board

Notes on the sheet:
Nano-SIM (HDM 4.3)
LTE antenna (HDM 5.3)
GNSS active antenna (HDM 6.2, fig. 6-2)

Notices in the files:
README.md:
License:
Phần | License
Phần mềm: `mcu/`, `shared/`, `simulator/`, `linux/`, `tools/`, `run.sh`, tài liệu | [MIT](LICENSE)
Thiết kế phần cứng: `hardware/` (sơ đồ, PCB, thư viện LFX, script sinh mạch) | [CERN-OHL-P v2](hardware/LICENSE)
Ngoại lệ: file mang header bản quyền riêng giữ nguyên license của chúng.
- `mcu/bsp/*/board.h`, `iomux.h`: Rockchip, Apache-2.0.
- `linux/dts/*.dts`: dựa trên DTS của Luckfox, GPL-2.0+ OR MIT.
SDK Luckfox / Rockchip, datasheet và tài liệu của Luckfox **không** nằm trong repo; tải từ nguồn chính thức.
Dự án thử nghiệm, **không có bảo đảm**. Dron
